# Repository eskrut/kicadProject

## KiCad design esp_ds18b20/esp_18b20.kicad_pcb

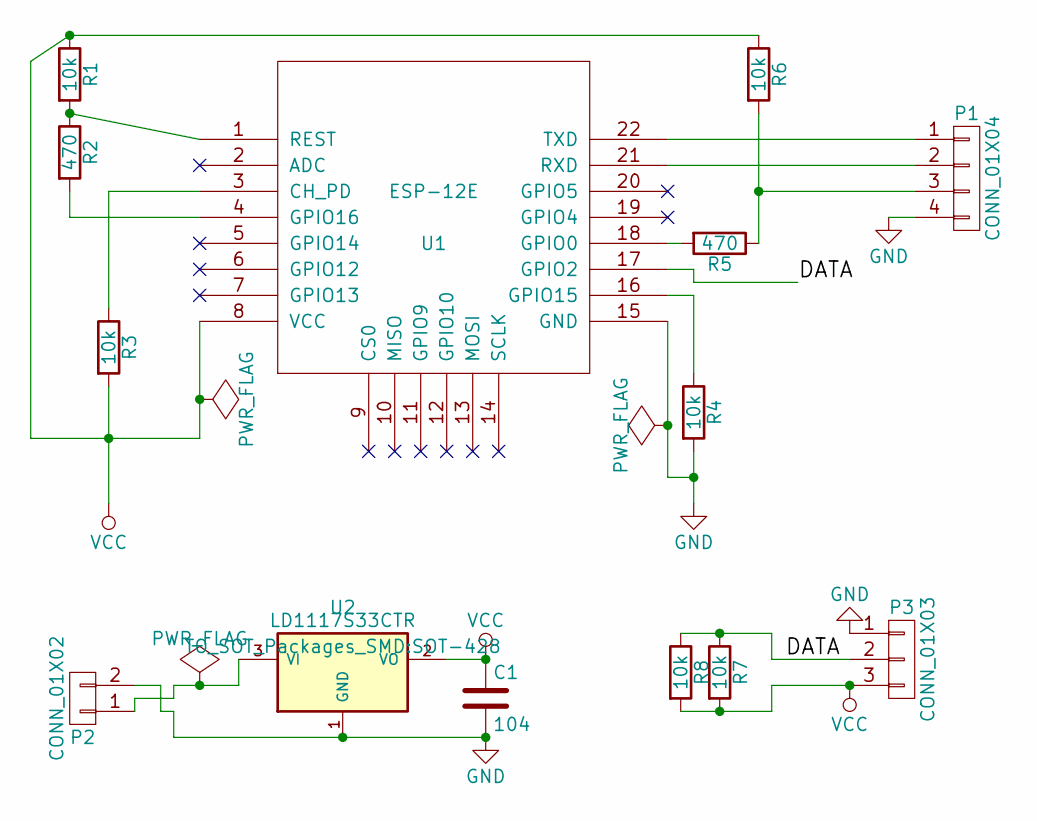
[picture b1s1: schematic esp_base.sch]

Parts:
C1: 104; C_Disc_D6_P5
P1: CONN_01X04; Pin_Header_Angled_1x04
P2: CONN_01X02; Pin_Header_Angled_1x02
P3: CONN_01X03; Pin_Header_Straight_1x03
R1, R3, R4, R6, R7, R8: 10k; R_0805_HandSoldering
R2, R5: 470; R_0805_HandSoldering
U1: ESP-12E
U2: LD1117S33CTR; SOT-428

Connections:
/DATA: P3.2, R7.1, R8.1, U1.17 (GPIO2)
GND: C1.2, P1.4, P2.2, P3.1, R4.2, U1.15 (GND), U2.1 (GND)
unnamed: P1.1, U1.22 (TXD)
unnamed: P1.2, U1.21 (RXD)
unnamed: P1.3, R5.1, R6.2
unnamed: P2.1, U2.3 (VI)
unnamed: R1.2, R2.1, U1.1 (REST)
unnamed: R2.2, U1.4 (GPIO16)
unnamed: R3.1, U1.3 (CH_PD)
unnamed: R4.1, U1.16 (GPIO15)
unnamed: R5.2, U1.18 (GPIO0)
VCC: C1.1, P3.3, R1.1, R3.2, R6.1, R7.2, R8.2, U1.8 (VCC), U2.2 (VO)

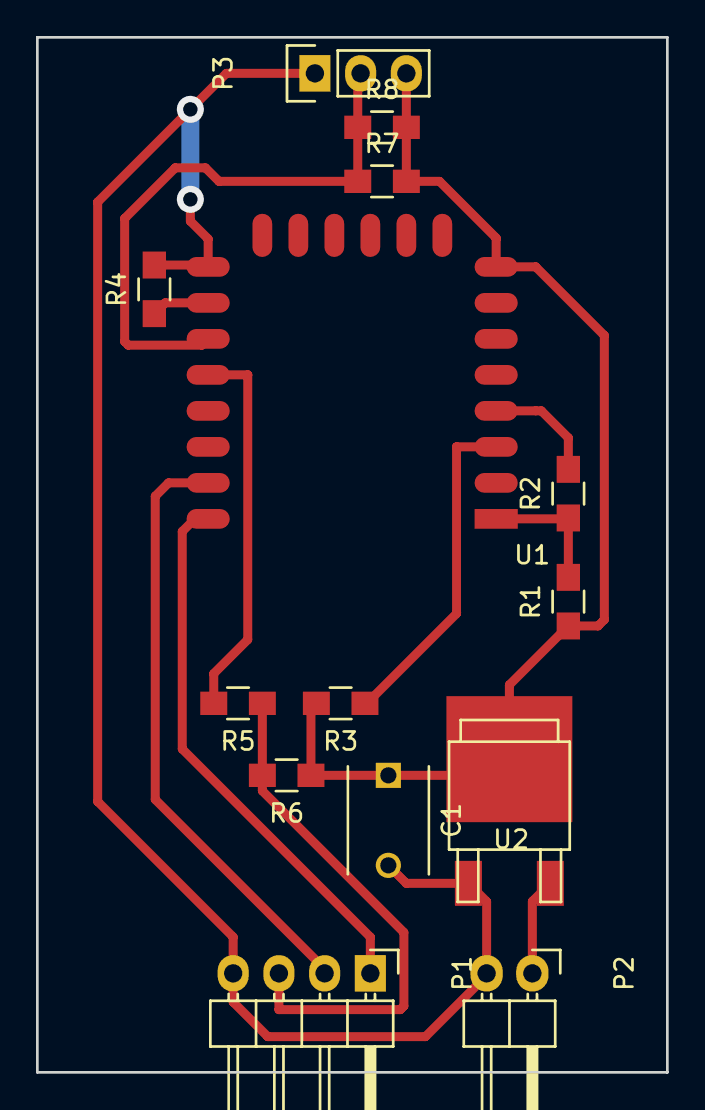
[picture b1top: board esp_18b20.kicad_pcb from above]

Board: 2 copper layers, 35.0 x 57.5 mm, 14 parts (0 on the bottom side), 12 nets.

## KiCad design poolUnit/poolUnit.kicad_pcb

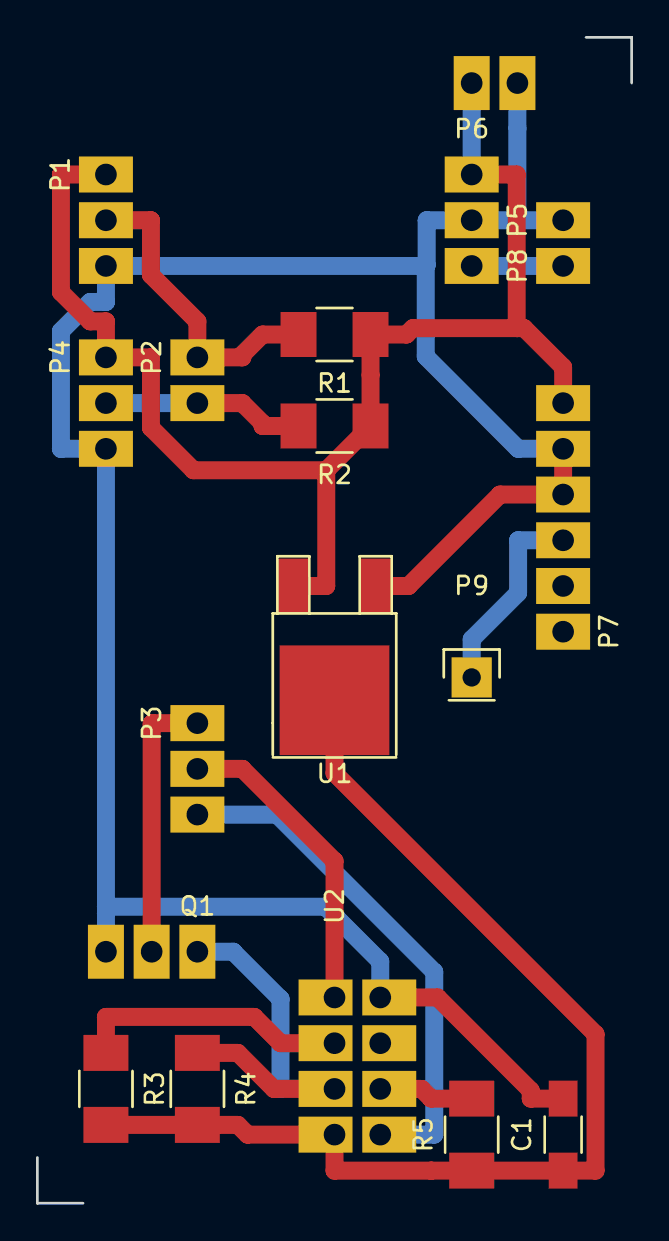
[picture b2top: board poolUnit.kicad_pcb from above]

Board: 2 copper layers, 33.0 x 64.8 mm, 18 parts (0 on the bottom side), 13 nets.

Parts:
C1: 0.1mu; C_1206_HandSoldering
P1: WATER_DS; Pin_1x3_hand_soldering
P2: A_DS; Pin_1x2_hand_soldering
P3: A_ESP; Pin_1x3_hand_soldering
P4: AIR_DS; Pin_1x3_hand_soldering
P5: RST; Pin_1x2_hand_soldering
P6: POWER; Pin_1x2_hand_soldering
P7: PH_MODULE; Pin_1x6_hand_soldering
P8: A_POWER; Pin_1x3_hand_soldering
P9: A_PH; Pin_Header_Straight_1x01
Q1: BC547; Pin_1x3_hand_soldering
R1, R2: 4.7K; R_1210_HandSoldering
R3, R4, R5: 10K; R_1210_HandSoldering
U1: LD1117S33CTR; TO-252-2Lead
U2: ESP-01v090; Pin_2x4_hand_soldering

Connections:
+3V3: C1.1, R3.2, R4.2, R5.1, U1.2, U2.7
+5V: P1.1, P4.1, P6.1, P7.6, P8.3, R1.1, R2.1, U1.3
/A_DATA: P2.2, P4.2, R2.2
/ESP_RESET: P3.1, Q1.2
/PH_DATA: P7.3, P9.1
/RX_1: P3.2, U2.1
/TX_1: P3.3, U2.8
/W_DATA: P1.2, P2.1, R1.2
GND: C1.2, P1.3, P4.3, P5.1, P6.2, P7.4, P7.5, P8.2, Q1.3, U1.1, U2.2
unnamed: P5.2, P8.1
unnamed: Q1.1, R4.1, U2.5
unnamed: R3.1, U2.3
unnamed: R5.2, U2.6
